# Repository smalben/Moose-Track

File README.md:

# Moose-Track

This is a shooting helpy thing

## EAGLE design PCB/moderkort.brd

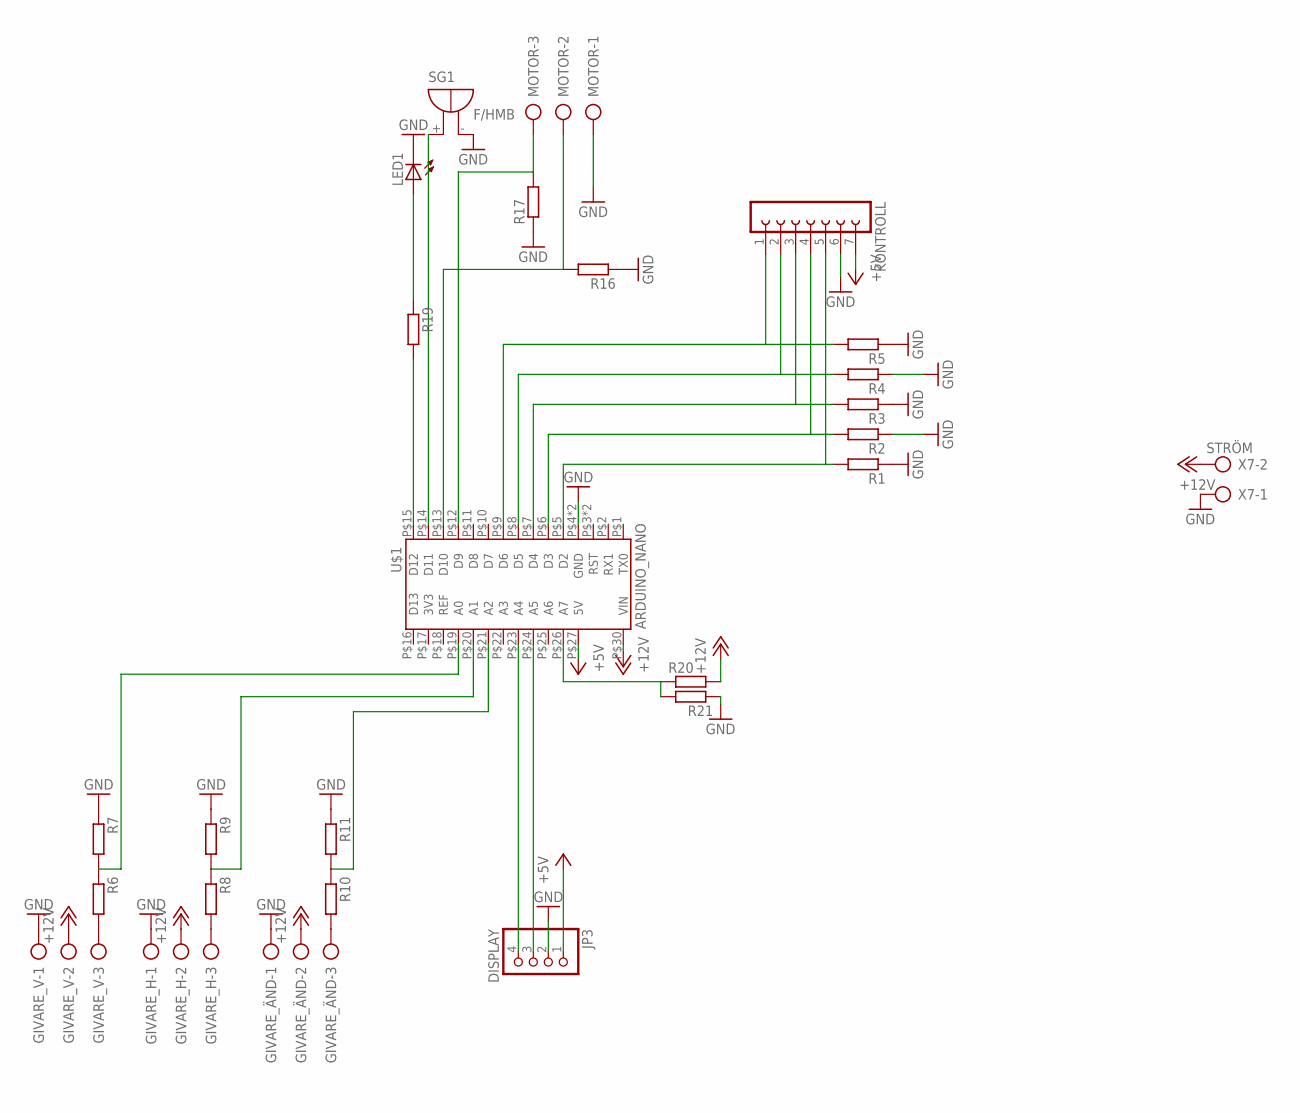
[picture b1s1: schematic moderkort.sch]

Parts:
GIVARE_H: AK500/3
GIVARE_V: AK500/3
GIVARE_ÄND: AK500/3
JP3: DISPLAY; 1X04
KONTROLL: FE07-1; FE07
LED1: LED5MM
MOTOR: AK500/3
R1, R2, R3, R4, R5, R6, R7, R8, R9, R10, R11, R16, R17, R19, R20, R21: R-EU_M1206; M1206
SG1: F/HMB
U$1: ARDUINO_NANO
X7: STRÖM; AK500/2

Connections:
+5V: JP3.1, KONTROLL.7, U$1.P$27 (5V)
+12V: GIVARE_H.2, GIVARE_V.2, GIVARE_ÄND.2, R20.2, U$1.P$30 (VIN), X7.2
GND: GIVARE_H.1, GIVARE_V.1, GIVARE_ÄND.1, JP3.2, KONTROLL.6, LED1.K (C), MOTOR.1, R1.1, R2.1, R3.1, R4.1, R5.1, R7.1, R9.1, R11.1, R16.1, R17.1, R21.1, SG1.-, U$1.P$4 (GND), U$1.P$29 (GND), X7.1
unnamed: LED1.A, R19.1
unnamed: GIVARE_V.3, R6.2
unnamed: R6.1, R7.2, U$1.P$19 (A0)
unnamed: GIVARE_H.3, R8.2
unnamed: R8.1, R9.2, U$1.P$20 (A1)
unnamed: GIVARE_ÄND.3, R10.2
unnamed: R10.1, R11.2, U$1.P$21 (A2)
unnamed: MOTOR.3, R17.2, U$1.P$12 (D9)
unnamed: JP3.3, U$1.P$24 (A5)
unnamed: JP3.4, U$1.P$23 (A4)
unnamed: R19.2, U$1.P$15 (D12)
unnamed: KONTROLL.5, R1.2, U$1.P$5 (D2)
unnamed: KONTROLL.4, R2.2, U$1.P$6 (D3)
unnamed: KONTROLL.3, R3.2, U$1.P$7 (D4)
unnamed: KONTROLL.2, R4.2, U$1.P$8 (D5)
unnamed: KONTROLL.1, R5.2, U$1.P$9 (D6)
unnamed: SG1.+, U$1.P$14 (D11)
unnamed: MOTOR.2, R16.2, U$1.P$13 (D10)
unnamed: R20.1, R21.2, U$1.P$26 (A7)

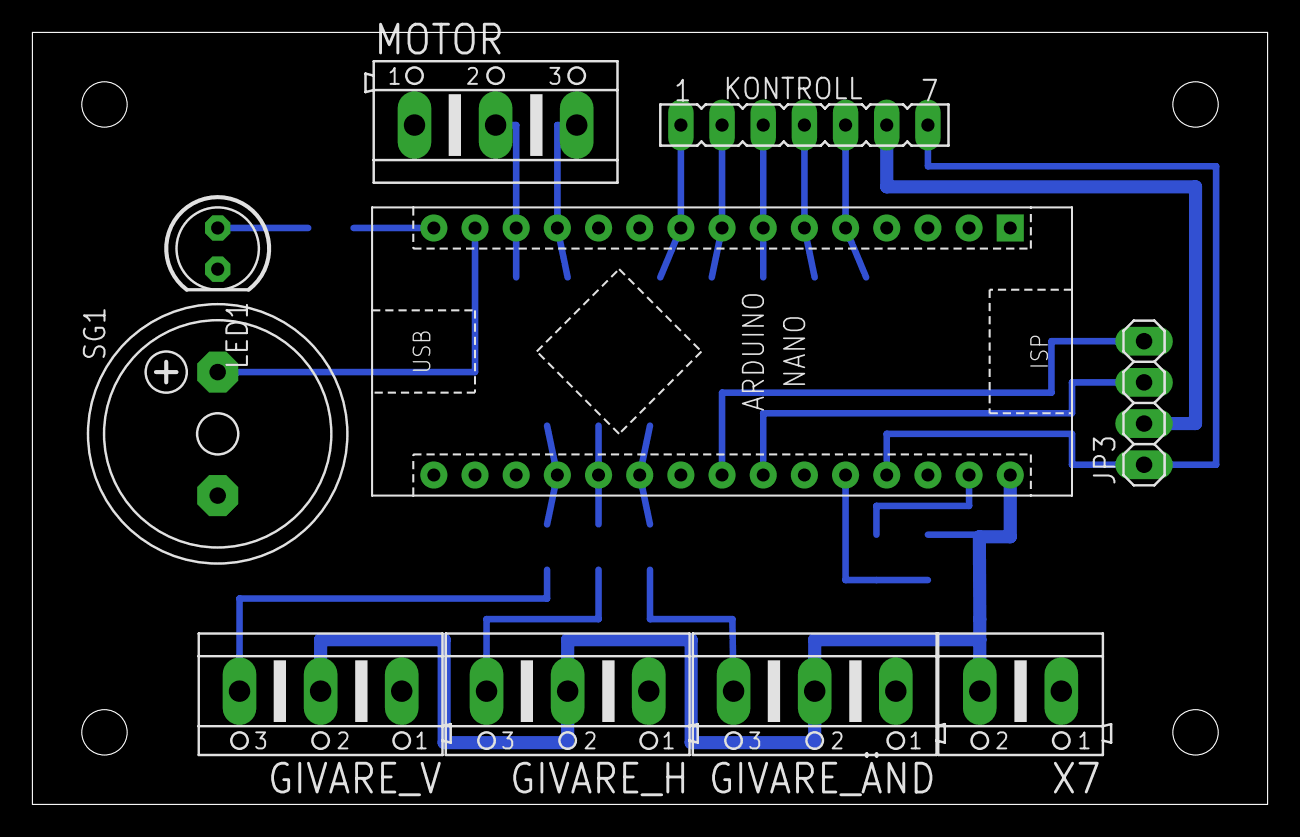
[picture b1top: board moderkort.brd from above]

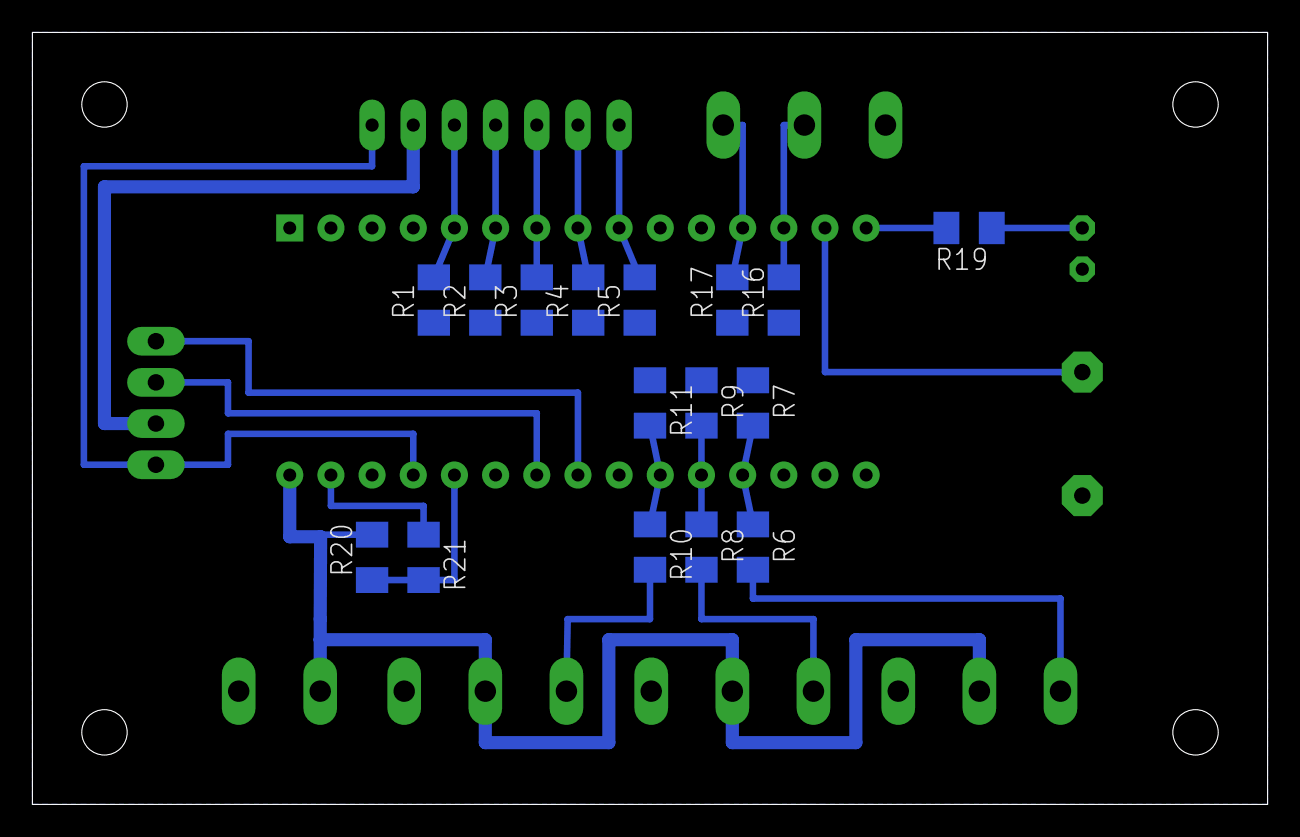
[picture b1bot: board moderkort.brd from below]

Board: 2 copper layers, 76.2 x 47.6 mm, 26 parts (16 on the bottom side), 22 nets.

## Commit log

2018-02-24 Changed the readme file
2018-02-24 Added project Arduino files
2018-02-24 Added documentation and CAD files
